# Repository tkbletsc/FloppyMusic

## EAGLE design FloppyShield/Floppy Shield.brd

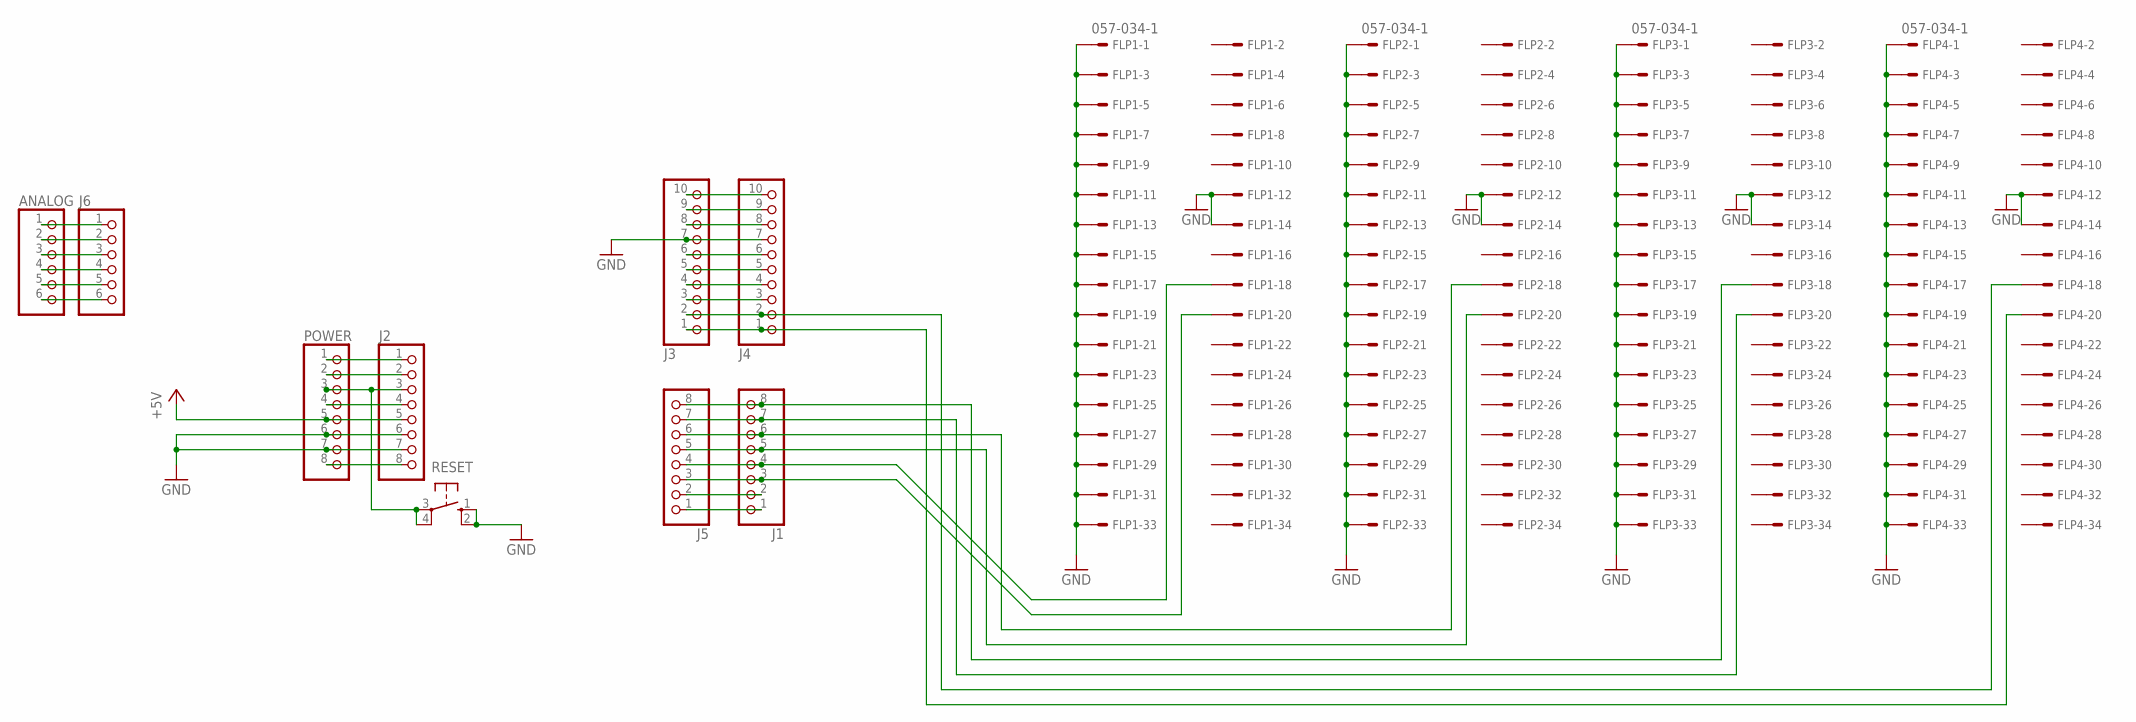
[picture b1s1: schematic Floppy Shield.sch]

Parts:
ANALOG: PINHD-1X6; 1X06
FLP1, FLP2, FLP3, FLP4: 057-034-1
J1, J2, J5: PINHD-1X8TH; 1X08-TH
J3, J4: PINHD-1X10TH; 1X10-TH
J6: PINHD-1X6; 1X06
POWER: PINHD-1X8TH; 1X08-TH
RESET: 10-XX; B3F-10XX

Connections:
+5V: J2.5, POWER.5
+9V: J2.8, POWER.8
GND: FLP1.1, FLP1.3, FLP1.5, FLP1.7, FLP1.9, FLP1.11, FLP1.12, FLP1.13, FLP1.14, FLP1.15, FLP1.17, FLP1.19, FLP1.21, FLP1.23, FLP1.25, FLP1.27, FLP1.29, FLP1.31, FLP1.33, FLP2.1, FLP2.3, FLP2.5, FLP2.7, FLP2.9, FLP2.11, FLP2.12, FLP2.13, FLP2.14, FLP2.15, FLP2.17, FLP2.19, FLP2.21, FLP2.23, FLP2.25, FLP2.27, FLP2.29, FLP2.31, FLP2.33, FLP3.1, FLP3.3, FLP3.5, FLP3.7, FLP3.9, FLP3.11, FLP3.12, FLP3.13, FLP3.14, FLP3.15, FLP3.17, FLP3.19, FLP3.21, FLP3.23, FLP3.25, FLP3.27, FLP3.29, FLP3.31, FLP3.33, FLP4.1, FLP4.3, FLP4.5, FLP4.7, FLP4.9, FLP4.11, FLP4.12, FLP4.13, FLP4.14, FLP4.15, FLP4.17, FLP4.19, FLP4.21, FLP4.23, FLP4.25, FLP4.27, FLP4.29, FLP4.31, FLP4.33, J2.6, J2.7, J3.7, J4.7, POWER.6, POWER.7, RESET.1 (S), RESET.2 (S1)
unnamed: J3.6, J4.6
unnamed: FLP4.20, J3.1, J4.1
unnamed: J3.4, J4.4
unnamed: J3.5, J4.5
unnamed: FLP1.18, J1.4, J5.4
unnamed: FLP2.18, J1.6, J5.6
unnamed: J3.3, J4.3
unnamed: FLP1.20, J1.3, J5.3
unnamed: FLP2.20, J1.5, J5.5
unnamed: FLP3.20, J1.7, J5.7
unnamed: FLP3.18, J1.8, J5.8
unnamed: J1.1, J5.1
unnamed: ANALOG.1, J6.1
unnamed: ANALOG.2, J6.2
unnamed: ANALOG.3, J6.3
unnamed: ANALOG.4, J6.4
unnamed: ANALOG.5, J6.5
unnamed: ANALOG.6, J6.6
unnamed: J1.2, J5.2
unnamed: FLP4.18, J3.2, J4.2
unnamed: J2.2, POWER.2
unnamed: J2.1, POWER.1
unnamed: J3.9, J4.9
unnamed: J3.10, J4.10
unnamed: J3.8, J4.8
unnamed: J2.4, POWER.4
RESET: J2.3, POWER.3, RESET.3, RESET.4 (P1)

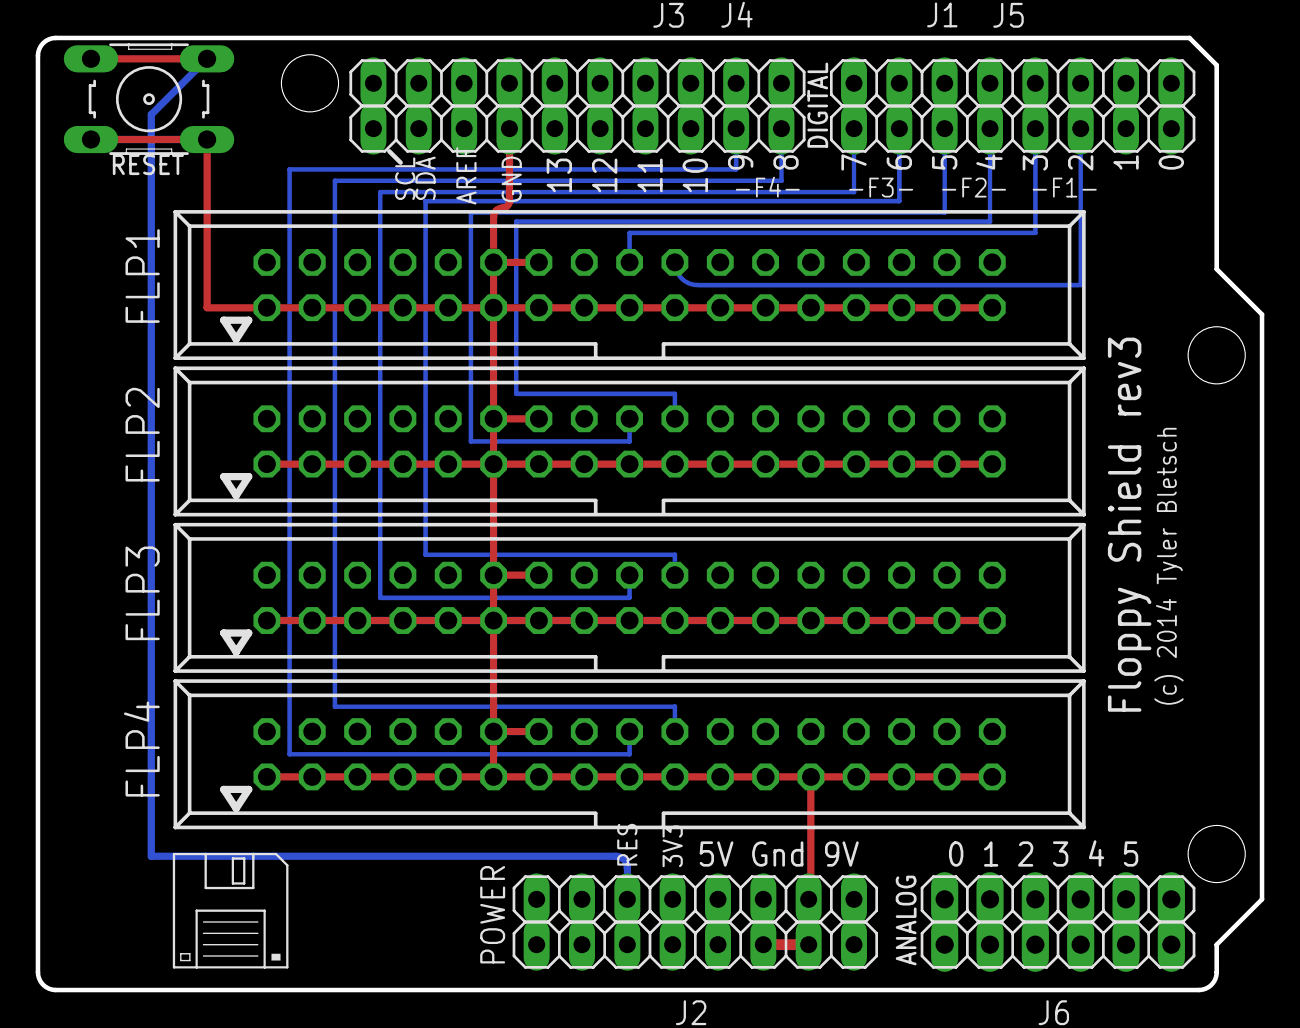
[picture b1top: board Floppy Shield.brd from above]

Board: 2 copper layers, 68.6 x 53.3 mm, 13 parts (0 on the bottom side), 30 nets.

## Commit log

2014-10-10 :confetti_ball: Added .gitattributes & .gitignore files
2014-10-10 Add initial
2014-10-12 Shield now works with "crossover" floppy cables (grounded DRIVE A SELECT)
2018-07-17 Use correct field separator in keywords.txt
    The Arduino IDE requires the use of a single true tab separator between the keyword name and identifier. When spaces are used rather than a true tab the keyword is not highlighted.
    Reference:
    https://github.com/arduino/Arduino/wiki/Arduino-IDE-1.5:-Library-specification#keywords

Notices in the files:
FloppyShield/Floppy Shield.brd:
(c) 2014 Tyler Bletsch
parts and their libraries:
SparkFun-Aesthetics: Licensing: Creative Commons ShareAlike 4.0 International - https://creativecommons.org/licenses/by-sa/4.0
